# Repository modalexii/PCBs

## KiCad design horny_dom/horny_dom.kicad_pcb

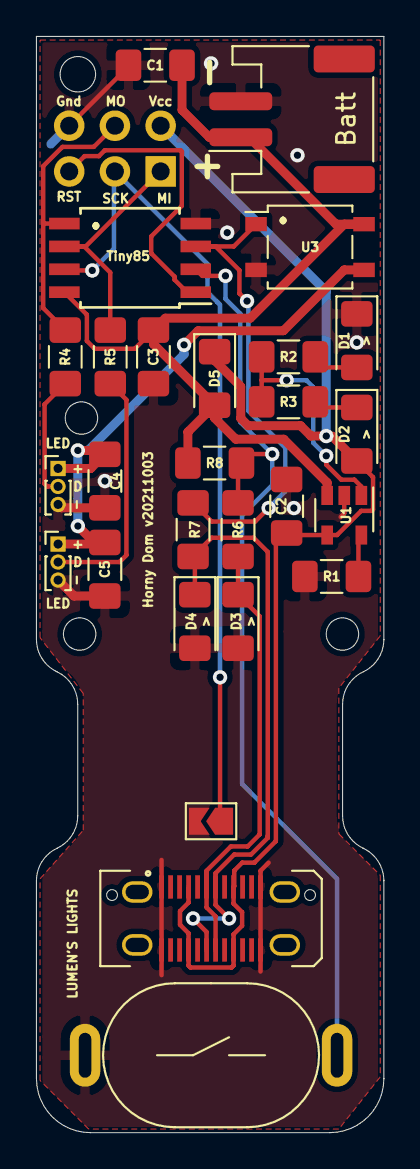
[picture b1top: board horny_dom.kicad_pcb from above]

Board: 2 copper layers, 19.3 x 60.9 mm, 28 parts (0 on the bottom side), 18 nets.

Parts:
BT1: Battery; JST_PH_S2B-PH-SM4-TB_1x02-1MP_P2.00mm_Horizontal
Batt: AVR-ISP-6; PinSocket_2x03_P2.54mm_Vertical
C1, C2: C; C_1206_3216Metric_Pad1.42x1.75mm_HandSolder
C3, C4, C5: C_Small; C_1206_3216Metric_Pad1.42x1.75mm_HandSolder
D1, D2: LED; LED_1206_3216Metric_Pad1.42x1.75mm_HandSolder
D3, D4: D_Zener_Small; D_1206_3216Metric_Pad1.42x1.75mm_HandSolder
D5: D_Small_ALT; D_1206_3216Metric_Pad1.42x1.75mm_HandSolder
J1: USB_C_Receptacle; USB_C_Receptacle_JAE_DX07S024WJ3R400
JP1: SolderJumper_2_Open; SolderJumper-2_P1.3mm_Open_TrianglePad1.0x1.5mm
LED: Conn_01x03_Male; PinHeader_1x03_P1.00mm_Vertical
LED#2: Conn_01x03_Male; PinHeader_1x03_P1.00mm_Vertical
R1, R2, R3, R4, R5, R6, R7, R8: R_Small; R_1206_3216Metric_Pad1.42x1.75mm_HandSolder
SW1: SW_Push; MXUTEUK_SelfLock_OnOff_Button_Switch
Tiny85: ATtiny85-20SU; SOIJ-8_5.3x5.3mm_P1.27mm
U1: MCP73831-2-OT; SOT-23-5
U3: ASSR-1218; SO-4_4.4x4.3mm_P2.54mm

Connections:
CHG_FULL_GREEN: D1.2, R2.2
CHG_PROG_RED: D2.1, R3.1
CHG_RATE_R: R1.2, U1.5
CHG_STAT: R2.1, R3.2, U1.1
FUTURE_USE_ISP_SCK: Batt.3, JP1.1, Tiny85.7
GND: BT1.2, Batt.6, C1.2, C2.1, C3.1, C4.2, C5.2, D1.1, D3.2, D4.2, J1.A1, J1.A12, J1.B1, J1.B12, JP1.2, LED.3, LED#2.3, R1.1, SW1.1, Tiny85.4, U1.2, U3.2
ISP_RST: Batt.5, Tiny85.1
LED_DAT_L_CLEAN: LED#2.2, R4.2
LED_DAT_L_ISC_MOSI: Batt.4, R4.1, Tiny85.5
LED_DAT_R_CLEAN: LED.2, R5.1
LED_DAT_R_ISC_MISO: Batt.1, R5.2, Tiny85.6
LEDv+: C4.1, C5.1, LED.1, LED#2.1, U3.3
MODE_BTN: R6.1, R8.1, SW1.2, Tiny85.2
SSR_LED_EN: R7.1, Tiny85.3, U3.1
USBDAT+: D3.1, J1.A6, J1.B6, R6.2
USBDDAT-: D4.1, J1.A7, J1.B7, R7.2
USBv+: Batt.2, C2.2, D2.2, D5.1, J1.A4, J1.A9, J1.B4, J1.B9, U1.4
batt+: BT1.1, C1.1, C3.2, D5.2, R8.2, Tiny85.8, U1.3, U3.4

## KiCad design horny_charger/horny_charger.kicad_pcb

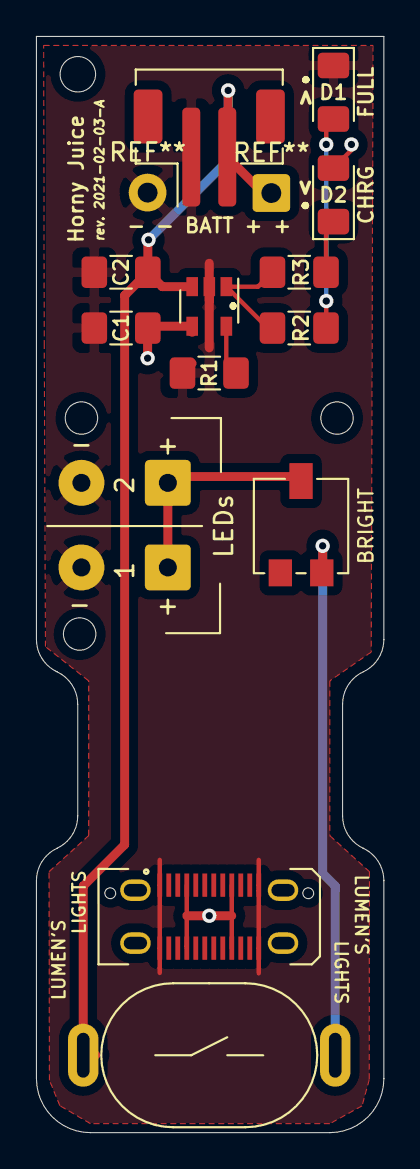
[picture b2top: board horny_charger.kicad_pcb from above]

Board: 2 copper layers, 19.3 x 60.9 mm, 12 parts (0 on the bottom side), 8 nets.

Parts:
BT1: Battery; JST_PH_B2B-PH-SM4-TB_1x02-1MP_P2.00mm_Vertical
C1, C2: C; C_1206_3216Metric_Pad1.42x1.75mm_HandSolder
D1, D2: LED; LED_1206_3216Metric_Pad1.42x1.75mm_HandSolder
J1: USB_C_Receptacle; USB_C_Receptacle_JAE_DX07S024WJ3R400
R1, R2, R3: R_Small; R_1206_3216Metric_Pad1.42x1.75mm_HandSolder
RV1: R_POT; Potentiometer_Vishay_TS53YL_Vertical
SW1: SW_DPST_x2; MXUTEUK_SelfLock_OnOff_Button_Switch
U1: MCP73831-2-OT; SOT-23-5

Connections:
+5V: C1.2, D2.2, J1.A4, J1.A9, J1.B4, J1.B9, U1.4
GND: BT1.1, C1.1, C2.2, D1.1, J1.A1, J1.A12, J1.B1, J1.B12, R1.1, U1.2
unnamed: D2.1, R3.2
batt-charge_in: BT1.2, C2.1, SW1.1, U1.3
charge_prog: R1.2, U1.5
charge_stat_r_to_led: D1.2, R2.2
charge_stat_to_r: R2.1, R3.1, U1.1
sw_to_r: RV1.1, SW1.2

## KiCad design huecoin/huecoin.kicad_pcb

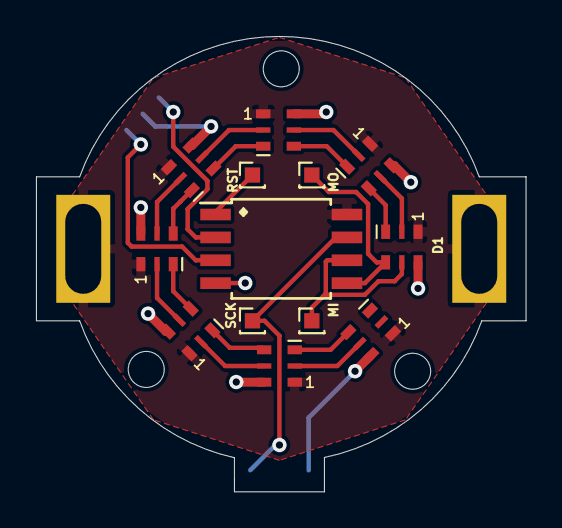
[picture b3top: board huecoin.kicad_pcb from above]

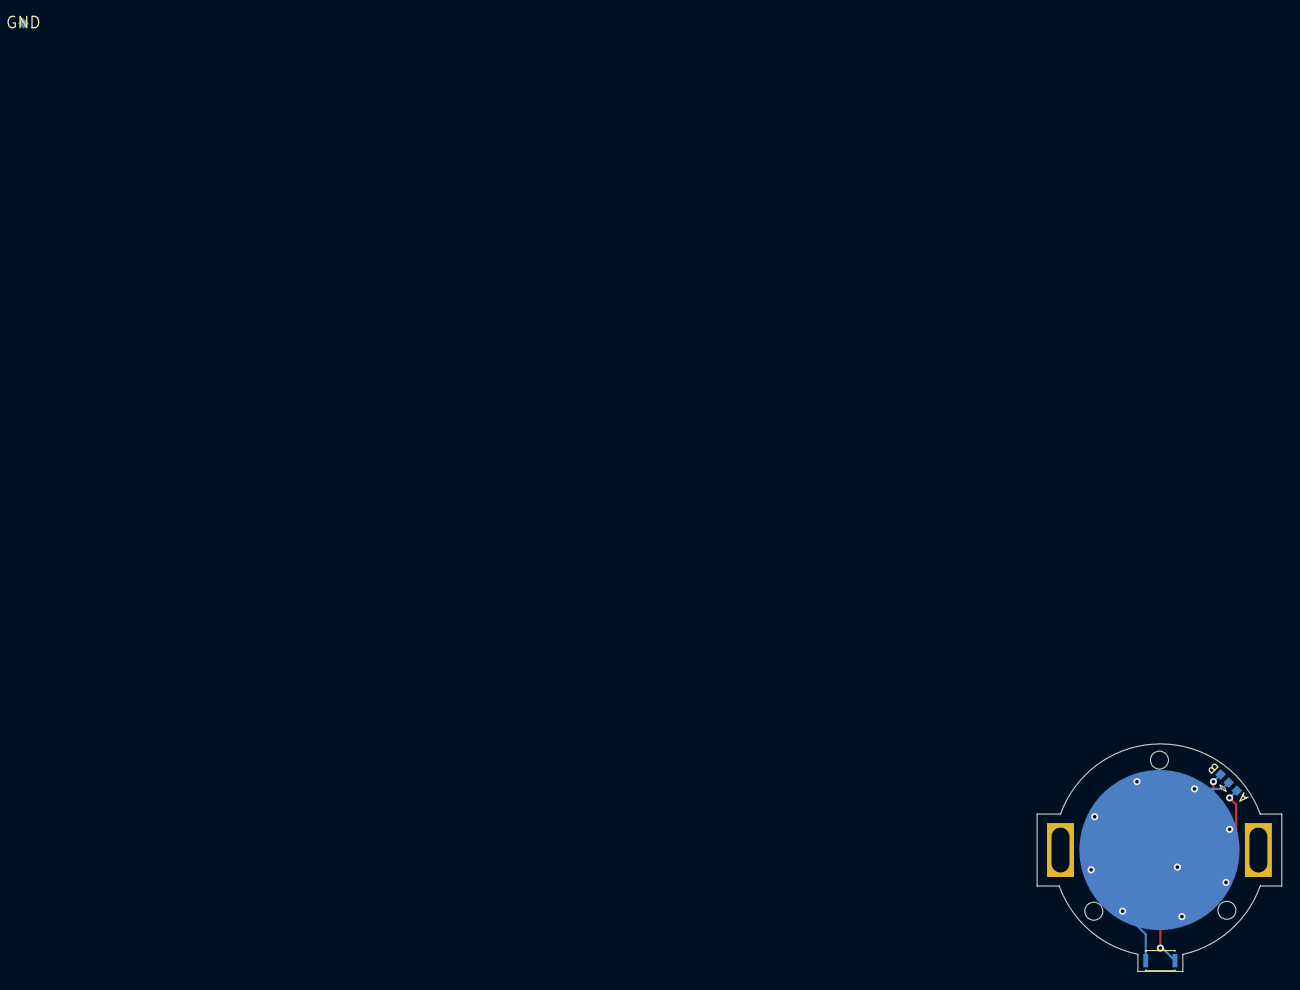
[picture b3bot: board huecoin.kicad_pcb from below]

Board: 2 copper layers, 27.2 x 25.3 mm, 19 parts (5 on the bottom side), 22 nets.

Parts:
.: ATtiny85-20SU; SOIJ-8_5.3x5.3mm_P1.27mm
BT1: Battery_Cell; BatteryHolder_Keystone_3002_1x2032
D1, D2, D3, D4, D5, D6, D7, D8: APA102-2020; LED-APA102-2020
GND: (no value)
MI: PinHeader_1x01_P1.00mm_Vertical
MO: PinHeader_1x01_P1.00mm_Vertical
RST: PinHeader_1x01_P1.00mm_Vertical
RST#2, RST#3, RST#4: PinHeader_1x01_P1.00mm_Vertical
SCK: PinHeader_1x01_P1.00mm_Vertical
SW1: SW_MEC_5G; SW_SPST_CK_KXT3

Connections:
+3V3: ..8, BT1.1, D1.1, D2.1, D3.1, D4.1, D5.1, D6.1, D7.1, D8.1
-3V3: ..4, BT1.2, D1.6, D2.6, D3.6, D4.6, D5.6, D6.6, D7.6, D8.6, RST#3.1, SW1.2
ICSP-MISO-LEDCLK: ..6, D1.5, MI.1
ICSP-MOSI-LEDDAT: ..5, D1.4, MO.1
ICSP-SCK-BTN: ..7, SCK.1, SW1.1
MODESEL1-SLEEP: ..2, RST#2.1
MODESEL2: ..3, RST.1
unnamed: D1.2, D2.5
unnamed: D1.3, D2.4
unnamed: D2.2, D3.5
unnamed: D2.3, D3.4
unnamed: D3.2, D4.5
unnamed: D3.3, D4.4
unnamed: D4.2, D5.5
unnamed: D4.3, D5.4
unnamed: D5.2, D6.5
unnamed: D5.3, D6.4
unnamed: D6.2, D7.5
unnamed: D6.3, D7.4
unnamed: D7.2, D8.5
unnamed: D7.3, D8.4
RESET: ..1, RST#4.1

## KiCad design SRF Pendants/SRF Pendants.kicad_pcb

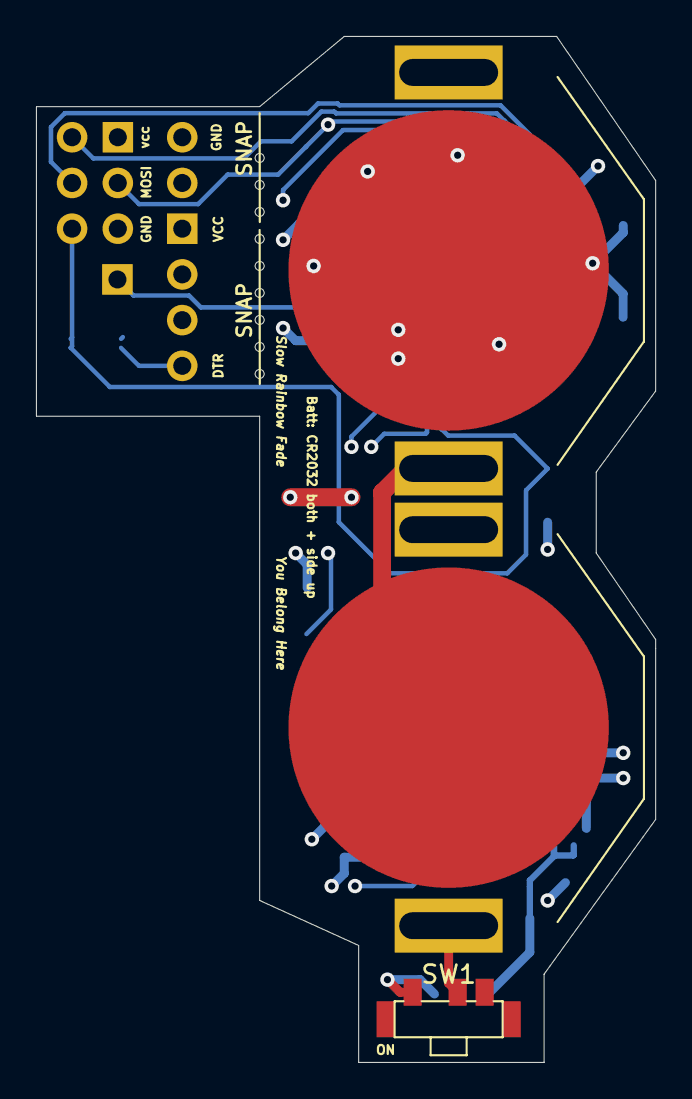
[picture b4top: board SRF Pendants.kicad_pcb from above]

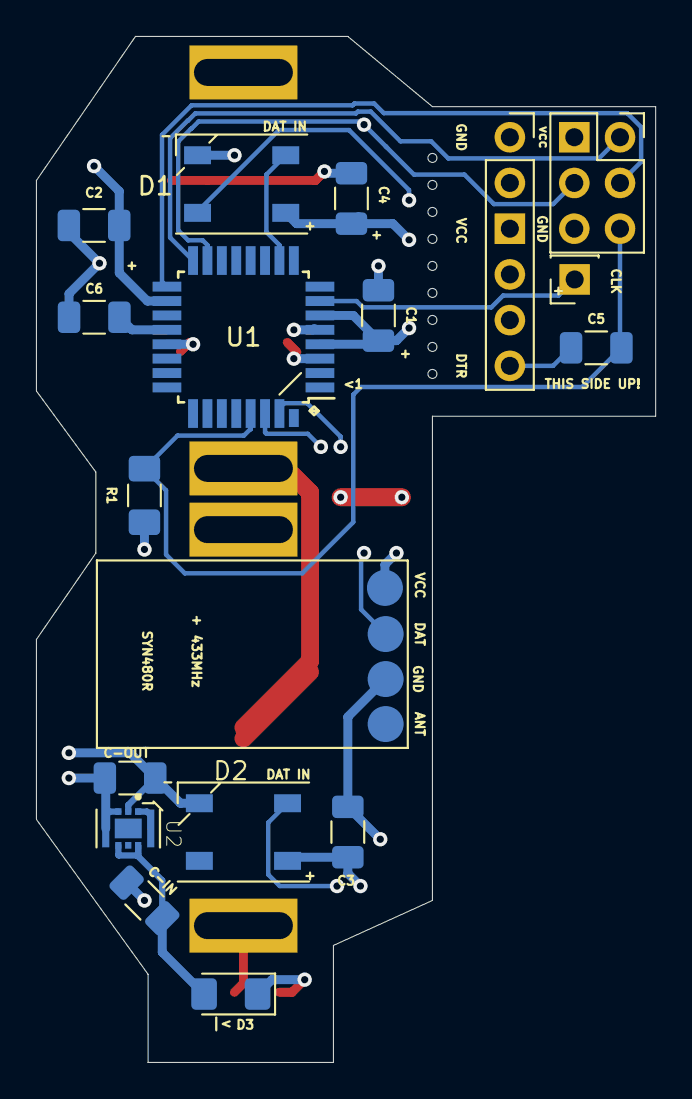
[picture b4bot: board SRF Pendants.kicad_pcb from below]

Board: 4 copper layers, 34.4 x 57.0 mm, 22 parts (17 on the bottom side), 16 nets.

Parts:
+: WS2812B; LED_SK6812_PLCC4_5.0x5.0mm_P3.2mm
BT1, BT1#2: Battery_Cell; BatteryHolder_Keystone_3002_1x2032
C1, C2, C3, C4, C5, C6: C_Small; C_1206_3216Metric
C-IN: C_Small; C_1206_3216Metric
C-OUT: C_Small; C_1206_3216Metric
D2: WS2812B; LED_SK6812_PLCC4_5.0x5.0mm_P3.2mm
D3: DIODE; D_1206_3216Metric_Pad1.42x1.75mm_HandSolder
H1: FTDIHeader; PinSocket_1x06_P2.54mm_Vertical
J1: AVR-ISP-6; PinSocket_2x03_P2.54mm_Vertical
R1: R; R_1206_3216Metric_Pad1.42x1.75mm_HandSolder
SW1: SW_SPST; UX0303_SPDP_SMD_Switch
U1: ATmega328P-AU; TQFP-32_7x7mm_P0.8mm
U2: XCL210C331GR-G; VREG_XCL220B283FR-G
U3: RF433-SYN480R; RF433_SYN480R
break-line-2.54mm, break-line-2.54mm#2: VAL**; snap-break-line-2.54mm

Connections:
DAT_LED-LED: +.2, D2.4
FTDI_RX: H1.4, U1.30
FTDI_TX: H1.5, U1.31
GND: +.1, BT1.2, C1.1, C2.1, C3.1, C4.2, C6.2, C-IN.2, C-OUT.1, D2.1, H1.1, J1.6, U1.3, U1.5, U1.21, U2.2, U3.3
LED1DIN: +.4, U1.10
MISO: J1.1, U1.16
MOSI: J1.4, U1.15, U3.2
unnamed: C5.1, H1.6
REGINDUCT1: U2.1, U2.7
RST: C5.2, J1.5, R1.2, U1.29
SCK: J1.3, U1.17
VBattSwitchedProtected: C-IN.1, D3.2, U2.4, U2.6
vBatt: BT1#2.1, SW1.2
vBattSeries: BT1.1, BT1#2.2
vBattSwitched: D3.1, SW1.3
vCC_REG: +.3, C1.2, C2.2, C3.2, C4.1, C6.1, C-OUT.2, D2.3, H1.3, J1.2, R1.1, U1.4, U1.6, U1.18, U1.20, U2.3, U2.8, U3.1

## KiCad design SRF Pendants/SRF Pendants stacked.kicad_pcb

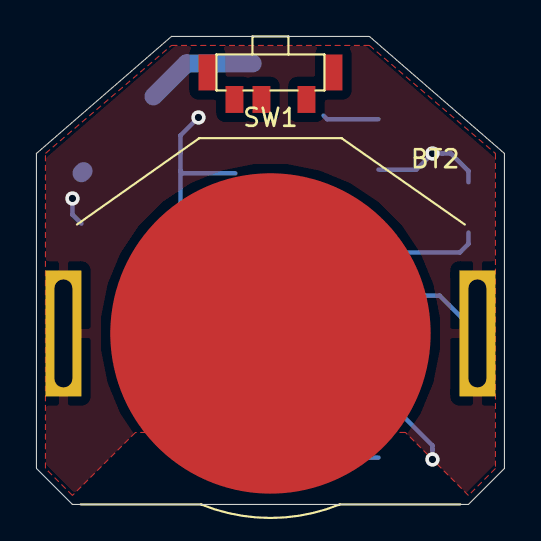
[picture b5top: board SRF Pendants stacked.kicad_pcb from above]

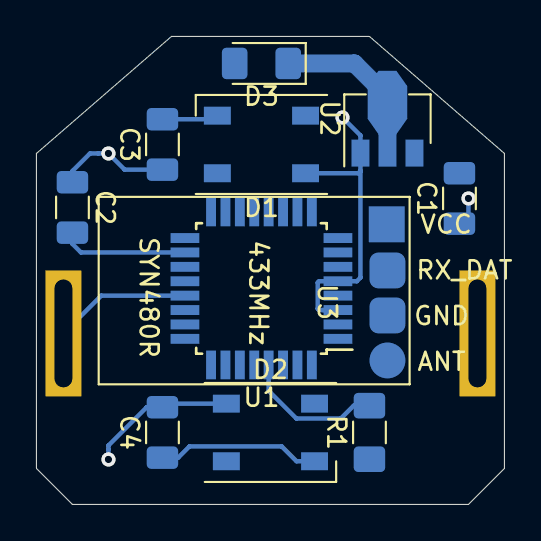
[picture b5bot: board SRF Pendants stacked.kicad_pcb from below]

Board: 2 copper layers, 26.0 x 26.0 mm, 13 parts (11 on the bottom side), 8 nets.

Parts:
BT2: Battery_Cell; BatteryHolder_Keystone_3002_1x2032
C1, C2, C3, C4: C_Small; C_1206_3216Metric
D1, D2: WS2812B; LED_SK6812_PLCC4_5.0x5.0mm_P3.2mm
D3: DIODE; D_1206_3216Metric_Pad1.42x1.75mm_HandSolder
R1: R; R_1206_3216Metric_Pad1.42x1.75mm_HandSolder
SW1: SW_SPST; UX0303_SPDP_SMD_Switch
U1: ATmega328P-AU; TQFP-32_7x7mm_P0.8mm
U2: AP2204RA-5.0; SOT-89-3
U3: RF433-SYN480R; RF433_SYN480R

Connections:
GND: BT2.1, C1.1, C2.1, C3.1, C4.2, D1.3, D2.3, U1.3, U1.5, U1.21, U2.1
LED1DIN: D1.4, U1.10
LEDDODI: D1.2, D2.4
unnamed: BT2.2, SW1.1
unnamed: D3.2, U2.2
unnamed: R1.2, U1.29
vBattSwitched: D3.1, SW1.2
vCC_REG: C1.2, C2.2, C3.2, C4.1, D1.1, D2.1, R1.1, U1.4, U1.6, U1.18, U2.3

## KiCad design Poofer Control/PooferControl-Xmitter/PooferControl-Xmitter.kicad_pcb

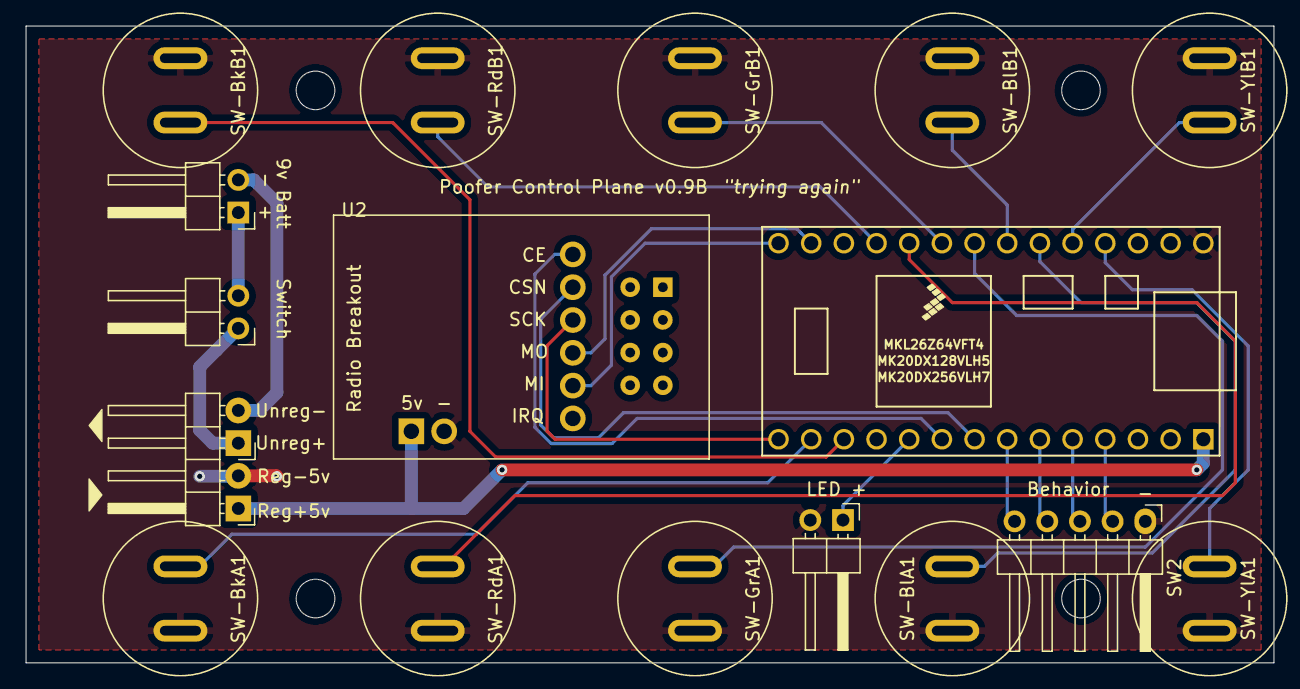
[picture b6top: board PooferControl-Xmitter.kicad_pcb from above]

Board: 2 copper layers, 97.0 x 49.5 mm, 17 parts (0 on the bottom side), 21 nets.

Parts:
BT1: Battery; PinHeader_1x02_P2.54mm_Horizontal
LED: PinHeader_1x02_P2.54mm_Horizontal
SW1: SW_SPST; PinHeader_1x02_P2.54mm_Horizontal
SW2: SW_Rotary1x4; PinHeader_1x05_P2.54mm_Horizontal
SW-BkA1: SW_Push_Dual_x2; PushButton_SPST_Momentary_Tactille_12mm
SW-BkB1: SW_Push_Dual_x2; PushButton_SPST_Momentary_Tactille_12mm
SW-BlA1: SW_Push_Dual_x2; PushButton_SPST_Momentary_Tactille_12mm
SW-BlB1: SW_Push_Dual_x2; PushButton_SPST_Momentary_Tactille_12mm
SW-GrA1: SW_Push_Dual_x2; PushButton_SPST_Momentary_Tactille_12mm
SW-GrB1: SW_Push_Dual_x2; PushButton_SPST_Momentary_Tactille_12mm
SW-RdA1: SW_Push_Dual_x2; PushButton_SPST_Momentary_Tactille_12mm
SW-RdB1: SW_Push_Dual_x2; PushButton_SPST_Momentary_Tactille_12mm
SW-YlA1: SW_Push_Dual_x2; PushButton_SPST_Momentary_Tactille_12mm
SW-YlB1: SW_Push_Dual_x2; PushButton_SPST_Momentary_Tactille_12mm
U1: TEC2-2411WI; PinHeader_1x04_P2.54mm_Horizontal
U2: NRF24L01_Breakout; nRF24L01_Breakout
uC1: Teensy32; Teensy30_31_32_LC

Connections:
/+5V: U1.1, U2.16, uC1.33
BEHAV: SW2.2, SW2.3, SW2.4, SW2.5, uC1.27, uC1.28, uC1.29, uC1.30
BkA: SW-BkA1.1, uC1.21
BkB: SW-BkB1.1, uC1.22
BlA: SW-BlA1.1, uC1.6
BlB: SW-BlB1.1, uC1.7
CE: U2.9, uC1.25
CSN: U2.10, uC1.26
GND: LED.2, SW2.1, SW-BkA1.1, SW-BkB1.1, SW-BlA1.1, SW-BlB1.1, SW-GrA1.1, SW-GrB1.1, SW-RdA1.1, SW-RdB1.1, SW-YlA1.1, SW-YlB1.1, U1.2, U2.15, uC1.1
GrA: SW-GrA1.1, uC1.8
GrB: SW-GrB1.1, uC1.9
LED: LED.1, uC1.24
MI: U2.13, uC1.14
MO: U2.12, uC1.13
unnamed: BT1.1, SW1.1, SW1.2, U1.3
unnamed: BT1.2, U1.4
RdA: SW-RdA1.1, uC1.10
RdB: SW-RdB1.1, uC1.11
SCK: U2.11, uC1.20
YlA: SW-YlA1.1, uC1.4
YlB: SW-YlB1.1, uC1.5

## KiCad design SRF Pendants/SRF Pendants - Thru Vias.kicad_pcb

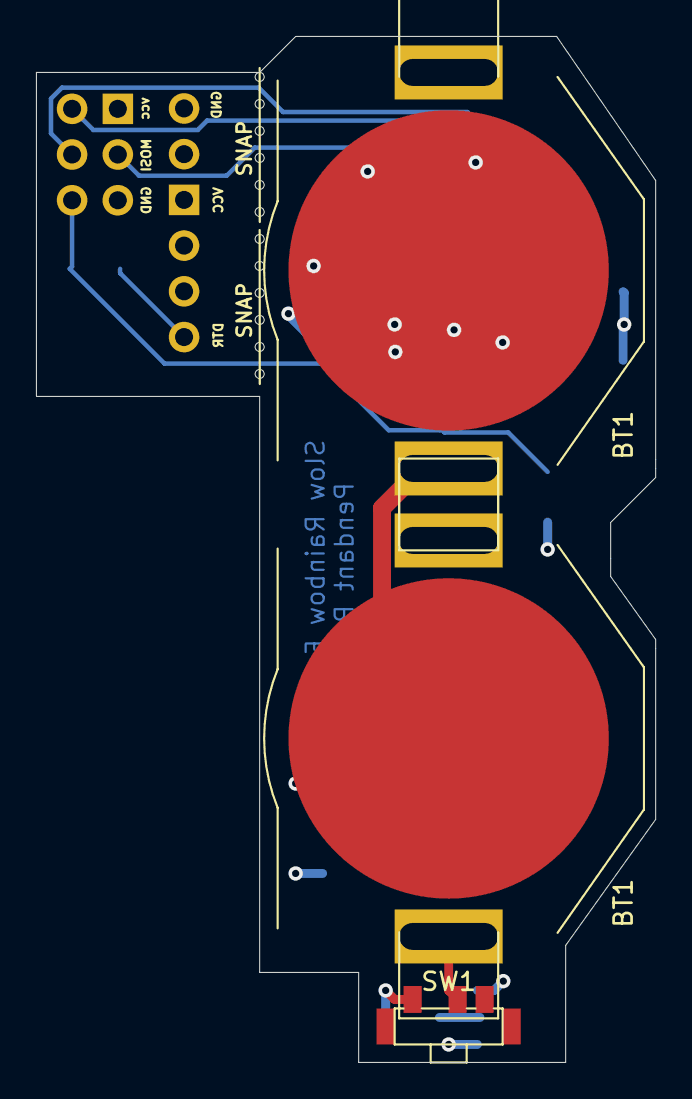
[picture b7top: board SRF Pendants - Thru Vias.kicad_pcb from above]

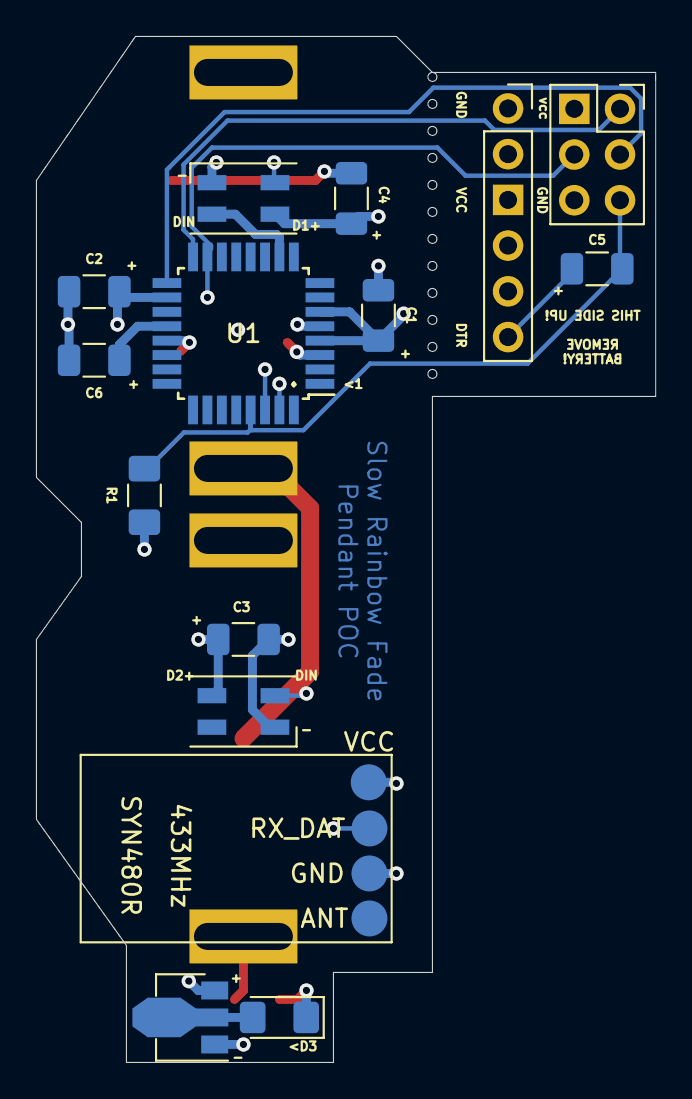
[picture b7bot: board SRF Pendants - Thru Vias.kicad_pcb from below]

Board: 4 copper layers, 34.4 x 57.0 mm, 20 parts (15 on the bottom side), 16 nets.

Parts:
-: WS2812B; LED_SK6812MINI_PLCC4_3.5x3.5mm_P1.75mm
<D3: DIODE; D_1206_3216Metric_Pad1.42x1.75mm_HandSolder
BT1, BT1#2: Battery_Cell; BatteryHolder_Keystone_3002_1x2032
C1, C2, C3, C4, C5, C6: C_Small; C_1206_3216Metric
D1+: WS2812B; LED_SK6812MINI_PLCC4_3.5x3.5mm_P1.75mm
H1: FTDIHeader; PinSocket_1x06_P2.54mm_Vertical
J1: AVR-ISP-6; PinSocket_2x03_P2.54mm_Vertical
R1: R; R_1206_3216Metric_Pad1.42x1.75mm_HandSolder
SW1: SW_SPST; UX0303_SPDP_SMD_Switch
U1: ATmega328P-AU; TQFP-32_7x7mm_P0.8mm
U2: AP2204RA-5.0; SOT-89-3
U3: RF433-SYN480R; RF433_SYN480R
break-line-2.54mm, break-line-2.54mm#2: VAL**; snap-break-line-2.54mm

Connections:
DAT_LED-LED: -.4, D1+.2
FTDI_RX: H1.4, U1.31
FTDI_TX: H1.5, U1.30
GND: -.3, C1.1, C2.1, C3.1, C4.2, C6.2, D1+.3, H1.1, J1.6, U1.3, U1.5, U1.21, U2.1, U3.3
LED1DIN: D1+.4, U1.10
MISO: J1.1, U1.16
MOSI: J1.4, U1.15
unnamed: C5.1, H1.6
unnamed: C6.1, U1.20
RST: C5.2, J1.5, R1.2, U1.29
SCK: J1.3, U1.17
VBattSwitchedProtected: <D3.2, U2.2
vBatt: BT1.1, SW1.2
vBattSeries: BT1.2, BT1#2.1, BT1#2.2
vBattSwitched: <D3.1, SW1.3
vCC_REG: -.1, C1.2, C2.2, C3.2, C4.1, D1+.1, H1.3, J1.2, R1.1, U1.4, U1.6, U1.18, U2.3, U3.1

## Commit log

2022-01-31 Initial upload of design file archive
2022-01-31 upgrade to kicad6
